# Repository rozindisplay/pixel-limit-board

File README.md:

# pixel-limit-board
EDA: [KiCad](https://www.kicad.org/) (5.1.10)

The schematics and PCB layout for the pixel's limit sensor board

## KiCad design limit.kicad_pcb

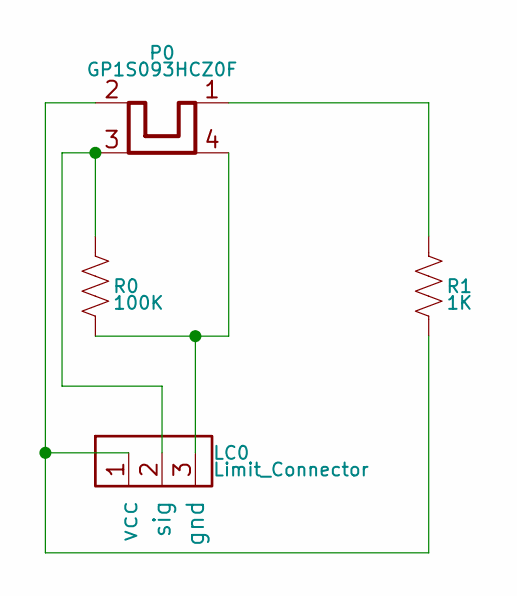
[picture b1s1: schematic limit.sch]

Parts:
LC0: Limit_Connector; JST_PH_S3B-PH-K_1x03_P2.00mm_Horizontal
P0: GP1S093HCZ0F
R0: 100K; R_Axial_DIN0207_L6.3mm_D2.5mm_P7.62mm_Horizontal
R1: 1K; R_Axial_DIN0207_L6.3mm_D2.5mm_P7.62mm_Horizontal

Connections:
unnamed: LC0.1 (vcc), P0.2, R1.2
unnamed: LC0.2 (sig), P0.3, R0.1
unnamed: LC0.3 (gnd), P0.4, R0.2
unnamed: P0.1, R1.1

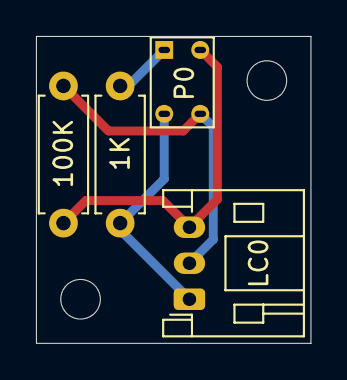
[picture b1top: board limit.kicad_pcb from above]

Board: 2 copper layers, 15.2 x 17.0 mm, 4 parts (0 on the bottom side), 4 nets.

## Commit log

2021-07-31 init
2021-07-31 removed unneeded ki artifact
2021-09-06 resistance changed from 10K to 1K ohms
